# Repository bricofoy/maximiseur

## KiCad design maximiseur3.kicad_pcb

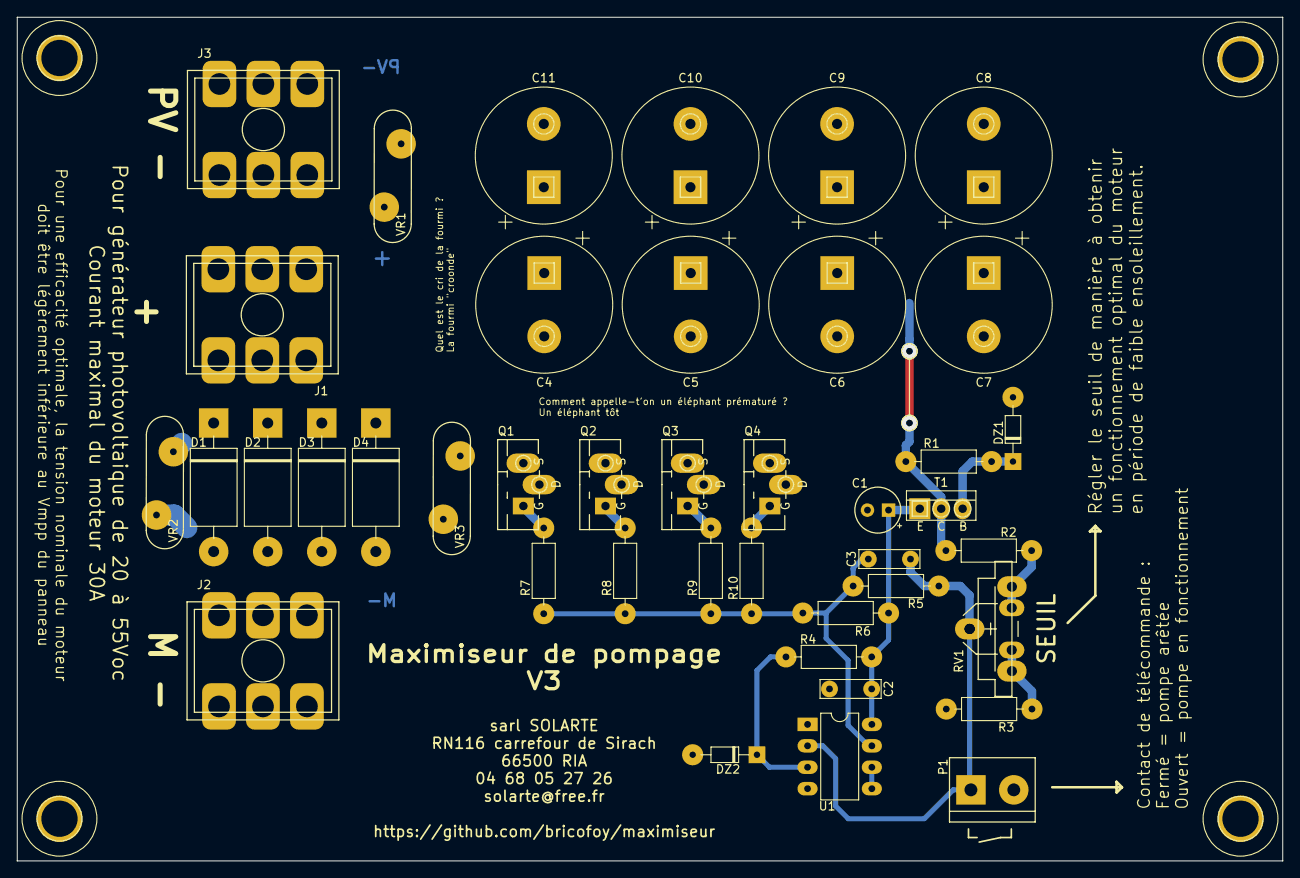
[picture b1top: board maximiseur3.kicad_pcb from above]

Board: 2 copper layers, 150.0 x 100.0 mm, 46 parts (0 on the bottom side), 15 nets.

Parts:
C1: 10µF; CP_Radial_D5.0mm_P2.50mm
C2: 100nF; C_Rect_L7.0mm_W2.0mm_P5.00mm
C3: 100pF; C_Rect_L7.0mm_W2.0mm_P5.00mm
C4, C5, C6, C7, C8, C9, C10, C11: 1000µF; CP_Radial_D16.0mm_P7.50mm
D1, D2, D3, D4: MUR420RL; D_DO-201AE_P15.24mm_Horizontal
DZ1: 12V; D_DO-34_SOD68_P7.62mm_Horizontal
DZ2: 6,2V; D_DO-34_SOD68_P7.62mm_Horizontal
H1, H2, H3, H4: MountingHole; MountingHole_4.3mm_M4
J1: PV+/M+; 7808
J2: M-; 7808
J3: PV-; 7808
P1: SW SW; bornier2
Q1, Q2, Q3, Q4: IRLB3036G; TO-220_FET-GDS_Vertical_LargePads_decales
R1, R4: 3k3; R_Axial_DIN0207_L6.3mm_D2.5mm_P10.16mm_Horizontal
R2: 15k; R_Axial_DIN0207_L6.3mm_D2.5mm_P10.16mm_Horizontal
R3: 2k2; R_Axial_DIN0207_L6.3mm_D2.5mm_P10.16mm_Horizontal
R5: 100k; R_Axial_DIN0207_L6.3mm_D2.5mm_P10.16mm_Horizontal
R6: 1k5; R_Axial_DIN0207_L6.3mm_D2.5mm_P10.16mm_Horizontal
R7, R8, R9, R10: 150; R_Axial_DIN0207_L6.3mm_D2.5mm_P10.16mm_Horizontal
RV1: 2k; Potentiometer_VishaySpectrol-Econtrim-Type36T
Rv1: 2k; pot_vert_Radiohm
T1: BD139; TO-126-3_Vertical
U1: LM311; DIP-8_W7.62mm_LongPads
VR1, VR2, VR3: V56ZA8; RV_Disc_D15.5mm_W4.5mm_P7.5mm

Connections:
/+15V: C1.1, C2.1, R4.1, R6.1, T1.1, U1.8
/M+: C4.1, C5.1, C6.1, C7.1, C8.1, C9.1, C10.1, C11.1, D1.1, D2.1, D3.1, D4.1, J1.1, R1.1, R2.1, T1.2, VR1.1, VR2.1
/M-: D1.2, D2.2, D3.2, D4.2, J2.1, Q1.D, Q2.D, Q3.D, Q4.D, VR2.2, VR3.1
/PV-: C1.2, C2.2, C4.2, C5.2, C6.2, C7.2, C8.2, C9.2, C10.2, C11.2, DZ1.2, DZ2.2, J3.1, P1.2, Q1.S, Q2.S, Q3.S, Q4.S, R3.2, U1.1, U1.4, VR1.2, VR3.2
/RC: C3.2, P1.1, R5.2, RV1.2, Rv1.2, U1.2
unnamed: C3.1, R5.1, R6.2, R7.1, R8.1, R9.1, R10.1, U1.7
unnamed: DZ1.1, R1.2, T1.3
unnamed: DZ2.1, R4.2, U1.3
unnamed: Q1.G, R7.2
unnamed: Q2.G, R8.2
unnamed: Q3.G, R9.2
unnamed: Q4.G, R10.2
unnamed: R2.2, RV1.3, Rv1.3
unnamed: R3.1, RV1.1, Rv1.1
unnamed: U1.5, U1.6

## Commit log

2019-08-09 work in progress
2019-08-19 premiere version correcte du PCB
2019-08-19 ajout vue 3D
2019-08-19 ajout de varistances de protection, taille définitive du PCB
2019-08-19 modification PCB : trous de fixation + un peu de ménage
2019-08-19 ajout images schéma et pcb
2019-08-20 derniers ajustements sur serigraphie avant export
2019-08-21 ajout seconde empreinte pour le potentiomètre + pads plus larges + sérigraphie
2019-08-21 ajout image F_silks
2019-08-21 rotation image silks
2019-08-21 ajout fichiers gerber et perçage
2019-08-21 agrandissement plan de masse pour faciliter la gravure CNC
